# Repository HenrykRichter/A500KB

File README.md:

# A500KB
This project contains the material related to a custom Commodore Amiga Mechanical Keyboard. While the initial development target was the iconic Amiga 500, the keyboard also fits in A3000/A4000 (maybe also A2000) external keyboard enclosures. It features the ability to mount Mitsumi or Cherry switches. The Power, Drive and Caps-Lock LEDs are implemented as 7 individually configurable RGB LEDs. LED configuration is provided by an AmigaOS program that talks to the Keyboard over the regular connection. Headers for two additional low active input sources (e.g. HDD, Network) are also present.

The keyboard may be populated with two options of Switches and associated Keycaps. The first option are the tactile Mitsumi mechanical switches (E25-33-137) and original A2000/3000/4000 keycaps or A1200.net replica keycaps. Please note that the Mitsumi mechanical switches are quite rare. The second option for switches and keycaps is standard Cherry MX or compatibles. In that latter case, the keycaps for the original Amiga layout are hard to obtain. Recently, the user steveed on [Amibay](https://www.amibay.com/threads/amiga-mx-style-keycaps-pcbs.2446001/) has managed to get replica Amiga compatible keycaps ordered from SignaturePlastics. Consequently, the recent designs of the plate are targeted at Cherry MX compatible stabilizers. The PCB still accepts Mitsumi or Cherry MX (3 pin or 5 pin) compatible switches.

If building the full keyboard is not an option, a sub-project of A500KB might be of interest. The controller part of A500KB is also usable as standalone controller for classic Mitsumi keyboards (A500KB Mini). While that A500KB Mini approach won't give the benefit of mechanical switches, it'll offer the custom LED functionality of A500KB.

Please have a look at the README.md in PCB/ for ordering/building notes.

## Requirements

- Amiga 500 or A3000/A4000 keyboard case
- Main PCB and Switchplate PCB
- 96 Keyswitches (Mitsumi or Cherry)
- parts (including AT90USB1287, IS32FL3237, diodes, LEDs and passives)
- suitable LEDs need to be of ARGB type (analog, common anode) such as Würth 150141M173100, Brightek QBLP677-RGB or similar
- 3D Printed parts for LED light guides (transparent) and spacers

## Pictures

## Acknowledgements

Kicad 3D Models and original Footprints imported from:
https://github.com/perigoso/keyswitch-kicad-library

## History

Version 2 of the PCBs addresses several small issues with the prototype. Better fitment is provided for Costar style suports of the larger keys (Shift,Return,Space,Tab etc.). Also, those keys are rotated 90 degrees such that the wire of the supports gets better clearance. The plate PCB got positioning holes for the pins in the top cover of A3000/A4000 keyboards.  Some minor additions were done to the electronics, including larger Diodes and more pullup/down resistors. Version 4 (see below) addresses potential space issues with A500 cases and cabling headers.

A set of 3D printed parts to fit A500KB into the Checkmate external keyboard case has been added in Apr-2025. Please see [3DPrint](https://github.com/HenrykRichter/A500KB/tree/main/3DPrint/Checkmate_KB_Case) for STL files and guidance pictures.

## Caveats

Potential space issues in different styles of A500 cases affected early versions (up to V3) of the design, where the keyboard could only mounted with soldered cables in most A500 cases. Since V4e of the PCB design, the connector J4 has been moved so that it may be populated with an angled pin header and fit all A500 cases as well as external (A2000,A3000,A4000) cases.

## License
The PCB, it's design files and all support code (Amiga, Atmega) are licensed as [CC BY NC SA](https://creativecommons.org/licenses/by-nc-sa/4.0/deed.en).

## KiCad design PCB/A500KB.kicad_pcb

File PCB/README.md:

# A500KB Building Notes
This project contains the material related to a custom Commodore Amiga Mechanical Keyboard. While the initial development target was the iconic Amiga 500, the keyboard also fits in A3000/A4000 (maybe also A2000) external keyboard enclosures. It features the ability to mount Mitsumi or Cherry switches. The Power, Drive and Caps-Lock LEDs are implemented as 7 individually configurable RGB LEDs. LED configuration is provided by an AmigaOS program that talks to the Keyboard over the regular connection. Headers for two additional low active input sources (e.g. HDD, Network) are also present.

The two variants of the PCBs in this repository are discussed below. In a nutshell: order PCB and plate for the full keyboard or just the A500KBMini PCB for the standalone controller.

## A500KB (full)

### PCB ordering

**Caution** There are two styles of Keyboard and Plate designs. The one with the suffix "US" is designed specifically for large left Shift (2.75U) and the "BigAss" mirrored L style return key. Should your keycap set include an ISO-style return key (like in most of my pictures), please choose the variant without "US" suffix. See below for comparison pictures towards Keycap styles, if still unsure.

- 1 PCB from A500KB\_Gerber, 2 layer PCB in FR4, 1.2mm thickness for a little more space in bottom case (standard 1.6mm will still be compatible)
- 1 PCB from A500KBPlate\_Gerber, 1 layer PCB in FR4 or Alu, 1mm thickness for PCB or plate mounted MX stabilizers _OR_ A500KBPlate\_Gerber\_V2D.zip for Costar style stabilizers

Starting with V5, there is also a US version of PCB and Plate designs. The US variant includes a large LShift (2.75U) and a large Return (inverted L). Please note that the respective keycaps for ISO Keyboards will not fit on the US version and vice versa.

### 3D printing

The 3D printed parts are in the 3DPrint/ subfolder. Which of those files are to be printed depends on the target enclosure. Please note that bolts and nuts are required for mounting. 
The keyboard framing spacers are designed for countersunk M2.5 bolts with a total length of 5mm. 
The LED frame is to be mounted by flathead M2 bolts with a total length of 5mm and matching nuts.

As of A500KB V4, the 3D printed parts have been unified. The side spacers will fit A500 (and reproduction cases), as well as at least most of the external keyboard cases (tested: A2000,A3000,A4000 Mitsumi cases).

Four parts are designed for all keyboard types: 
- Keyboard\_Spacer\_L\_F2025  - left side of keyboard
- Keyboard\_Spacer\_R\_F2025  - right side of keyboard
- Keyboard\_Spacer\_VL\_F2025 - front left below spacebar
- Keyboard\_Spacer\_VR\_F2025 - front right below cursor keys

A500
- Keyboard\_LEDs\_Rahmen - frame for holding the LED lenses
- Keyboard\_LEDs - LED lenses to be printed (twice!) in transparent filament or resin. Keep infill low.

You also might consider to look at Spacebar\_ExtraSprings for Mitsumi mechanical based builds. This part allows to place additional springs under the space bar in the same way that was present with Mitsumi Amiga keyboards. 

Also of relevance for Mitsumi builds is Keyboard\_CapsLockLED to be printed in transparent filament or resin. This light guide is supposed to point towards the clear dot on the CapsLock key from underneath.

One CDTV Keyboard I came across had studs in its lower case which were about 2mm shorter than those of other 
A2000-4000 keyboards I encountered. The A500KB might sit a bit too low in such CDTV keyboard enclosures. Simply place
three 3D printed adapters of CDTVKeyboard\_Stud\_Adapter.stl on the top row studs in that case.

### Parts

- Please see schematics and/or A500KB.csv for the latest list. All needed components were marked active at the last check with common distributors (like Digikey or Mouser).
- The 7 RGB LEDs need to be of RGBA type (i.e. common Anode) and can be mounted as PLCC or with leads.
- Choose between D1 and D69, depending on switches and keycaps. For CherryMX switches (with SMD LED provision), D69 would be a good choice. D1 is better suited for Mitsumi switches and associated keycaps.
- C15/C16 are not needed.
- The 1x31 flat cable connector (J1) is not needed and stays unpopulated
- Screw-In PCB mounted stabilizers are recommended for Cherry MX and compatible
- see below for a description in which cases R6/R10/R11 need to be installed
- an iBOM is provided as PCB/bom/ibom.html as soldering aid. Please download before use.

### Building

- Solder the SMD components first. 
- Populate either D1 or D69 for CapsLock LED, not both. D2 as classic CapsLock LED is optional. D2 can also be disabled in firmware, if desired (i.e. populate R10 to disable D2).
- Install R6 with 390R for use of RGB LEDs at the positions of Power LED and Floppy LED. Leave R6 open when placing classic Commodore A500 Green/Orange or Red/Green LEDs.
- V3b/V4: install R11 when digital LEDs (SK9822 or APA102) are mounted to D70-D84. Leave R11 open, otherwise

After placing the SMD components, flash the ATMega firmware and verify that the keyboard PCB works.
- Option A) connect by USB to some PC and shorten the pins of the individual keys
- Option B) add A500 cable to J4 and test with AmigaTestKit or similar

Please note that diode reworking after the plate was placed and keyswitches were soldered is not a job I'd look forward to. Therefore, diode soldering and orientation should be verified before going further (!)

For CherryMX based builds, place the PCB mounted stabilizers including their wires in the next step. Screw-In type stabilizers should be preferred. 8U stabilizer wires are not commonly available. Hence, it might be necessary to custom-bend the spacebar wire (133.4mm wide, 1.5-1.6mm diameter).

Afterwards, the keyswitches may be added. It is suggested to place four keyswitches in the corners and one in the middle at first. This tends to help aligning the plate over the main PCB. 

Add the 3D printed spacers, LED frame and lenses.

Consider some electric short protection as the last step after fitment tests are done and possibly remaining THT parts (like J5) are in. For me, two layers of Kapton (or generic Polyimide) tape have been working well. The Kapton doesn't add significant thickness to the main PCB.

### PCB / Plate variant choice

The following pictures should help to decide which PCB and Plate variant to obtain. The critical part in this choice is the Return key, where the mounting points differ significantly between the international version (ISO) version and the US (ANSI) layout.

## A500KBMini

A500KBMini is a little less demanding in the build procedure. There is, however a showstopper for prospective builds. None of the shops I am aware of carries the 1x31 angled FFC connector to be required for A500 Mitsumi Keyboards. Scavenging from broken Mitsumi keyboards might be an option.

### PCB ordering

- 1 PCB from A500KBMini\_Gerber, 2 layer PCB in FR4, 1mm-1.6mm thickness 

### 3D Printing
- Keyboard\_LEDs\_Rahmen as frame for holding the LED lenses
- Keyboard\_LEDs LED lenses to be printed (twice!) in transparent filament or resin

### Parts

- Please see schematics and/or A500KB.csv for the latest list. Exclude the 58 Diodes used for NKRO on the full keyboard. Except from the FFC connector, all other needed components were marked active at the last check with common distributors (like Digikey or Mouser).
- The 6 RGB LEDs need to be of RGBA type (i.e. common anode) and can be mounted as PLCC or with leads.
- C15/C16 are not needed.
- The 1x31 flat cable connector (J1) needs to be obtained and fitted.
- R10/R11 stay unpopulated

### Building

- Solder the SMD components first. 
- Install R6 with 390R for use of RGB LEDs at the positions of Power LED and Floppy LED. Leave R6 open when placing classic A500 Green/Orange or Red/Green LEDs.

After placing the SMD components, flash the ATMega firmware and verify that the keyboard PCB works.

Add the 3D printed LED frame and lenses.

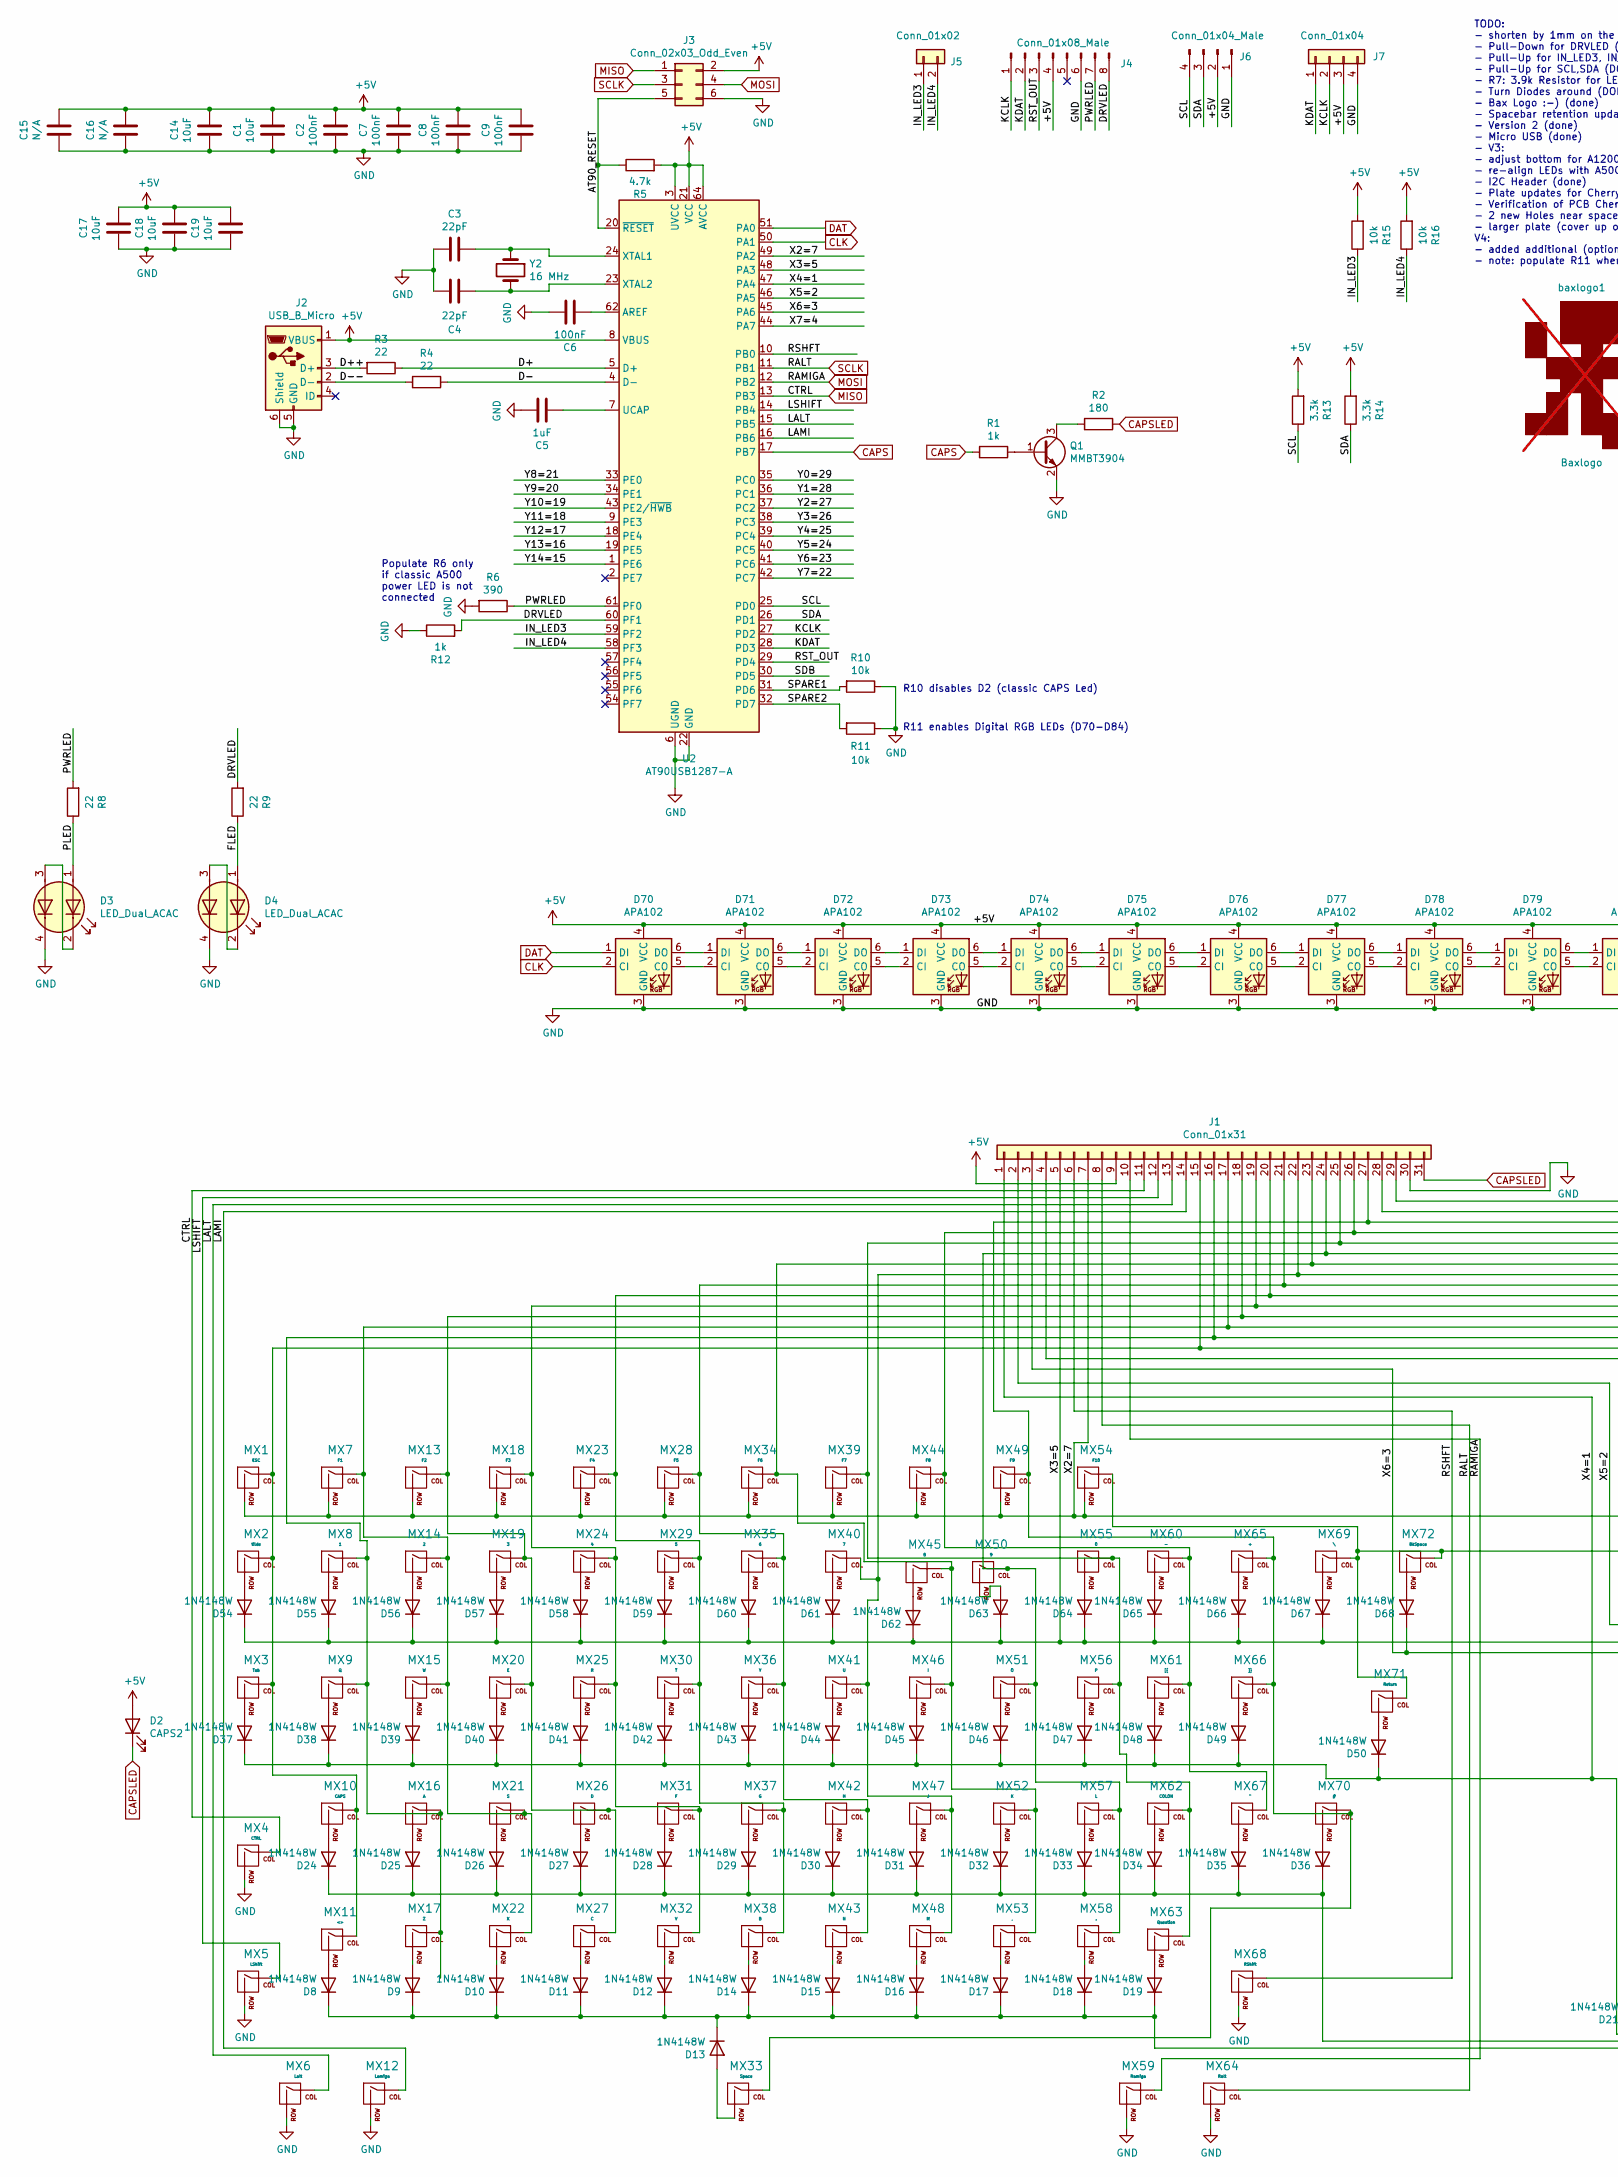
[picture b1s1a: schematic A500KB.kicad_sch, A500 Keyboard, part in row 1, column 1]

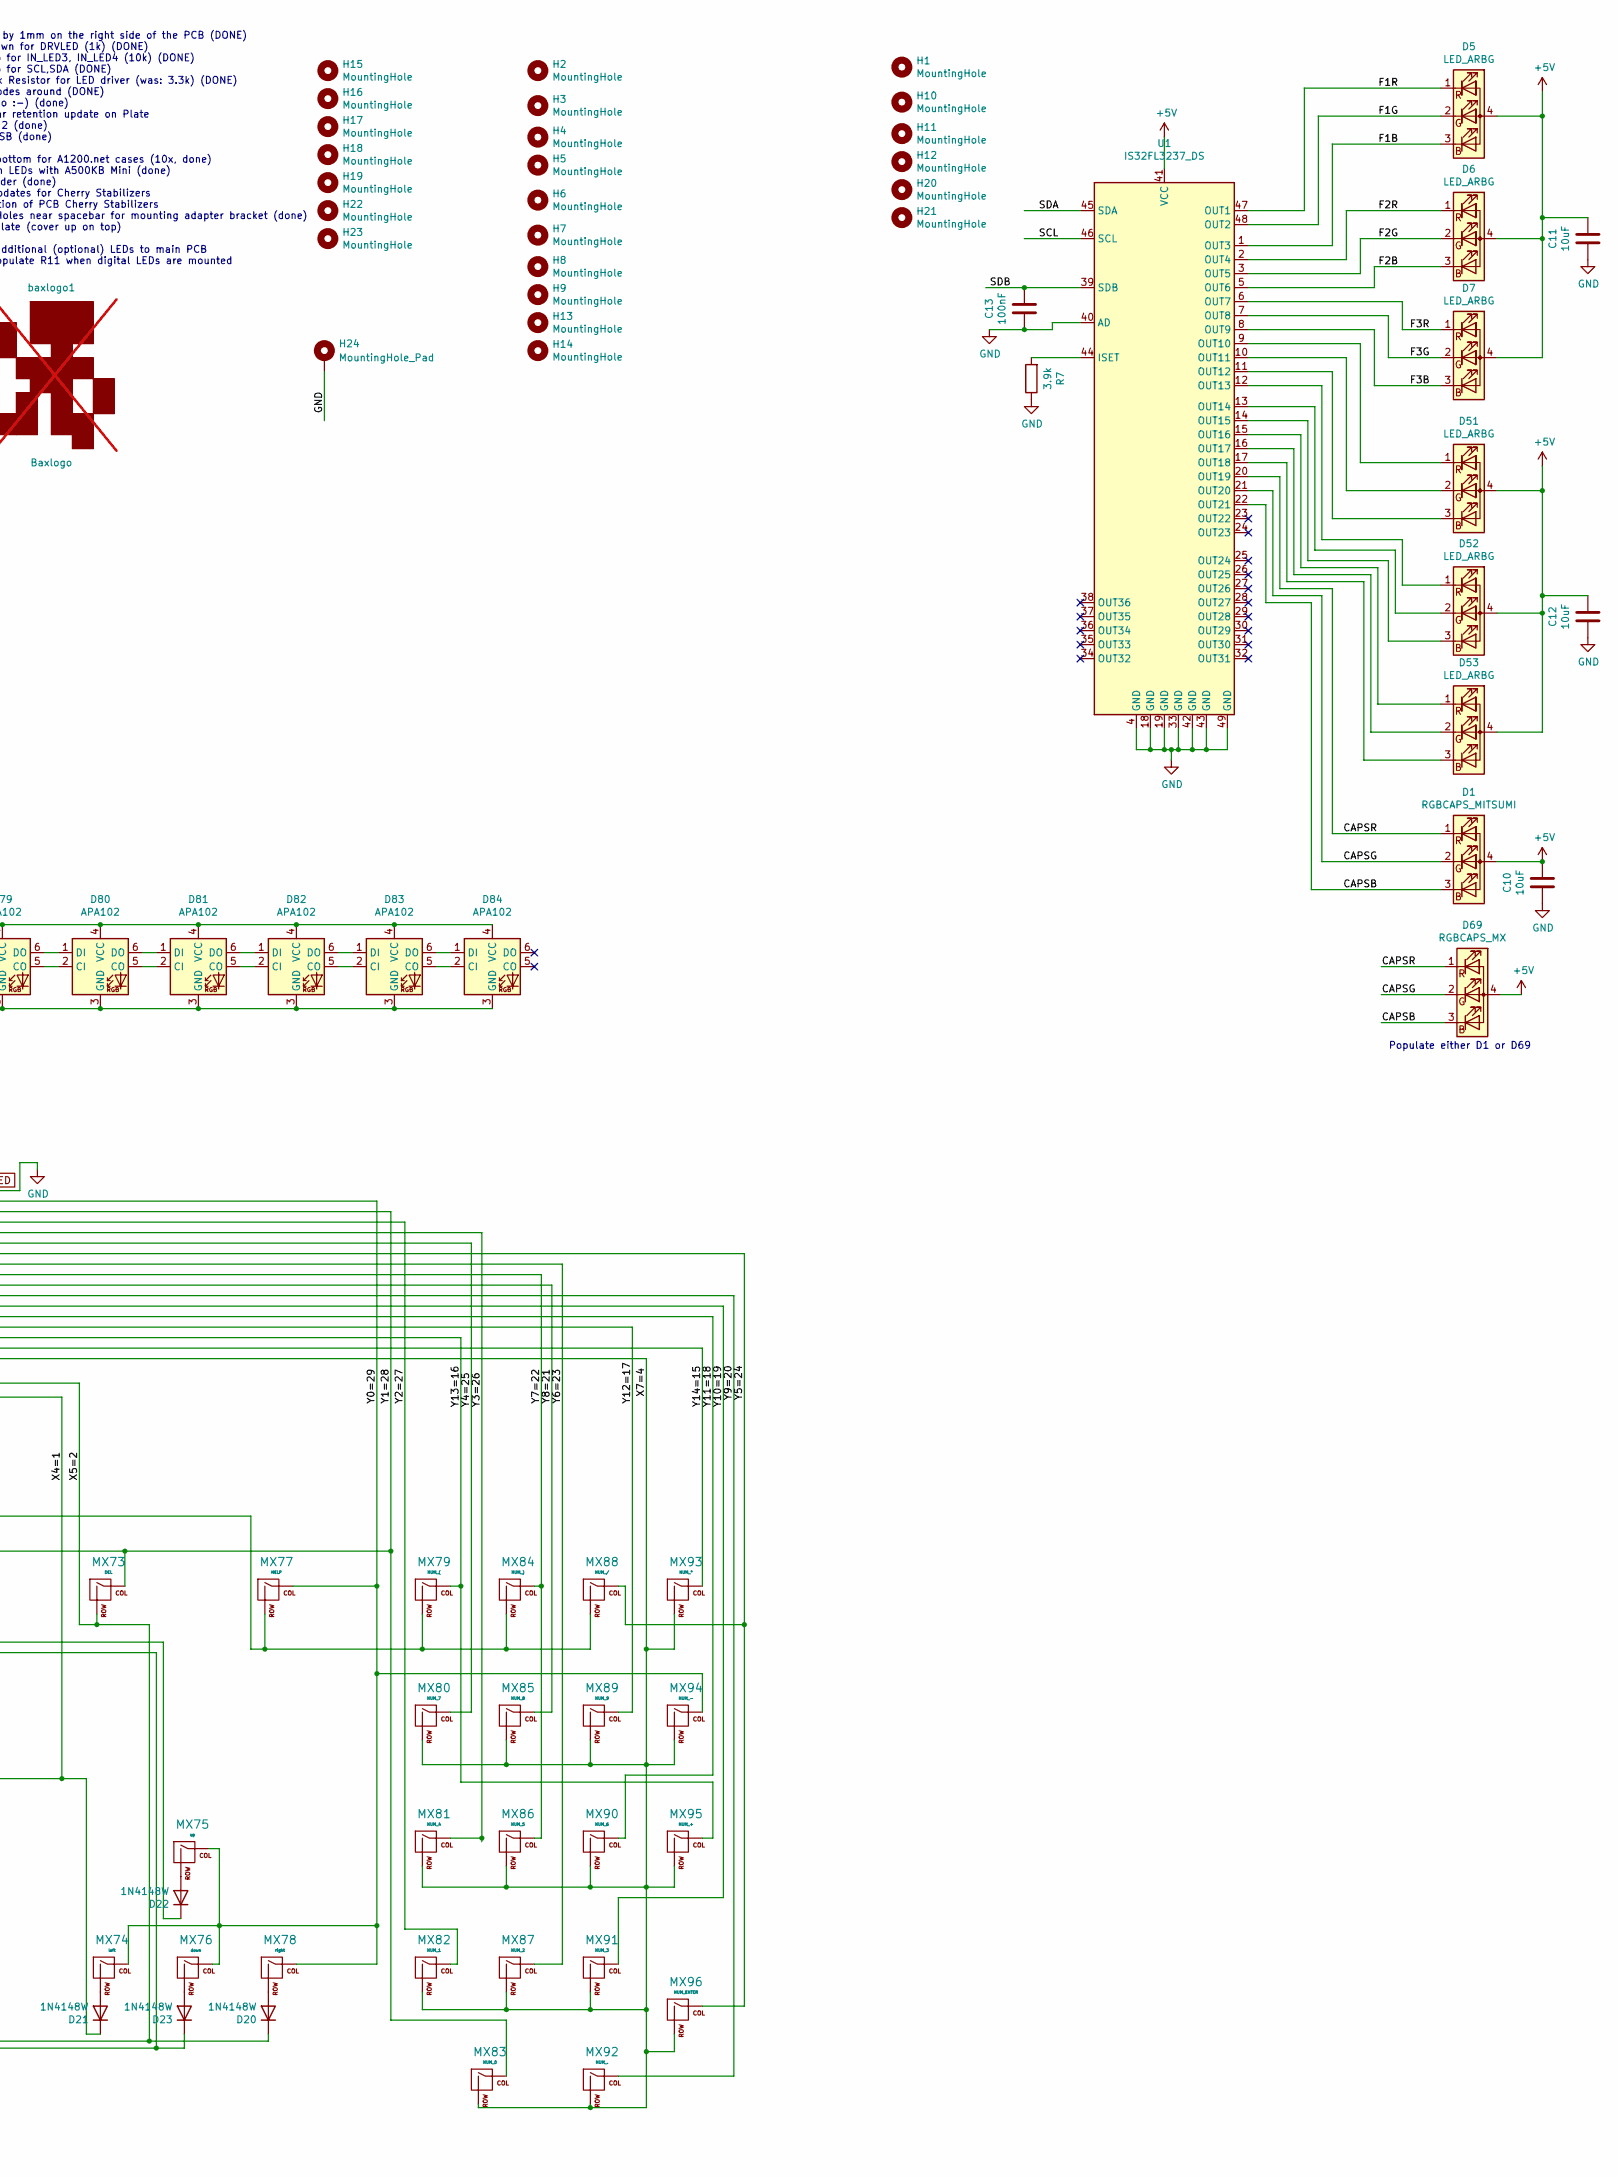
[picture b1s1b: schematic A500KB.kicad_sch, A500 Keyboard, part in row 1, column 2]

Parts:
C1, C10, C11, C12, C14, C17, C18, C19: 10uF; C_0805_2012Metric_Pad1.18x1.45mm_HandSolder; LCSC C15850
C2, C6, C7, C8, C9, C13: 100nF; C_0805_2012Metric_Pad1.18x1.45mm_HandSolder; LCSC C49678
C3, C4: 22pF; C_0805_2012Metric_Pad1.18x1.45mm_HandSolder; LCSC C1804
C5: 1uF; C_0805_2012Metric_Pad1.18x1.45mm_HandSolder; LCSC C28323
C15, C16: N/A; C_Elec_6.3x5.8
D1: RGBCAPS_MITSUMI; LED_Cree-PLCC4_3.2x2.8mm_CCW; digikey 732-4998-1-ND
D2: CAPS2; D_0805_2012Metric_Pad1.15x1.40mm_HandSolder; LCSC C688883
D3, D4: LED_Dual_ACAC; LED_DUAL_A500
D5: LED_ARBG; LED_Cree-PLCC4_3.2x2.8mm_CCW; digikey 1516-1195-1-ND
D6, D7, D51, D52, D53: LED_ARBG; LED_Cree-PLCC4_3.2x2.8mm_CCW; LCSC C5342281
D8, D9, D10, D11, D12, D13, D14, D15, D16, D17, D18, D19, D20, D21, D22, D23, D24, D25, D26, D27, D28, D29, D30, D31, D32, D33, D34, D35, D36, D37, D38, D39, D40, D41, D42, D43, D44, D45, D46, D47, D48, D49, D50, D54, D55, D56, D57, D58, D59, D60, D61, D62, D63, D64, D65, D66, D67, D68: 1N4148W; D_SOD-123; LCSC C444720
D69: RGBCAPS_MX; LED_Cree-PLCC4_3.2x2.8mm_CCW; digikey 732-4998-1-ND
D70, D71, D72, D73, D74, D75, D76, D77, D78, D79, D80, D81, D82, D83, D84: APA102; LED_RGB_5050-6; LCSC C5378730
H1, H2, H3, H4, H5, H6, H7, H8, H9, H10, H11, H12, H13, H14, H20, H21: MountingHole; MountingHole_3.2mm_M3_Small_Bax
H15, H16, H17, H18, H22, H23: MountingHole; MountingHole_2.5mm
H19: MountingHole; MountingHole_4.3mm_M4
H24: MountingHole_Pad; MountingHole_2.5mm_Pad_TopBottom
J1: Conn_01x31; FFC-1.25mm-Molex-39-53-2314
J2: USB_B_Micro; USB_Micro-B_Molex-105017-0001; Mouser 538-105017-0001
J3: Conn_02x03_Odd_Even; PinHeader_2x03_P2.54mm_Vertical; LCSC C32713276
J4: Conn_01x08_Male; PinHeader_1x08_P2.54mm_Vertical; LCSC C2935933
J5: Conn_01x02; PinHeader_1x02_P2.54mm_Vertical
J6: Conn_01x04_Male; PinHeader_1x04_P2.54mm_Vertical
J7: Conn_01x04; JST_EH_S4B-EH_1x04_P2.50mm_Horizontal; LCSC C265068
MX1: ESC; MXMitsumi-1U-NoLED
MX2: tilde; MXMitsumi-1.5U-NoLED
MX3: Tab; MXMitsumi-2U-NoLED
MX4: CTRL; MXMitsumi-1.25U-NoLED
MX5: LShift; MXMitsumi-1.75U-NoLED
MX6: Lalt; MXMitsumi-1.25U-NoLED
MX7: F1; MXMitsumi-1.25U-NoLED
MX8: 1; MXMitsumi-1U-NoLED
MX9: Q; MXMitsumi-1U-NoLED
MX10: CAPS; MXMitsumi-1U-NoLED
MX11: <>; MXMitsumi-1U-NoLED
MX12: Lamiga; MXMitsumi-1.25U-NoLED
MX13: F2; MXMitsumi-1.25U-NoLED
MX14: 2; MXMitsumi-1U-NoLED
MX15: W; MXMitsumi-1U-NoLED
MX16: A; MXMitsumi-1U-NoLED
MX17: Z; MXMitsumi-1U-NoLED
MX18: F3; MXMitsumi-1.25U-NoLED
MX19: 3; MXMitsumi-1U-NoLED
MX20: E; MXMitsumi-1U-NoLED
MX21: S; MXMitsumi-1U-NoLED
MX22: X; MXMitsumi-1U-NoLED
MX23: F4; MXMitsumi-1.25U-NoLED
MX24: 4; MXMitsumi-1U-NoLED
MX25: R; MXMitsumi-1U-NoLED
MX26: D; MXMitsumi-1U-NoLED
MX27: C; MXMitsumi-1U-NoLED
MX28: F5; MXMitsumi-1.25U-NoLED
MX29: 5; MXMitsumi-1U-NoLED
MX30: T; MXMitsumi-1U-NoLED
MX31: F; MXMitsumi-1U-NoLED
MX32: V; MXMitsumi-1U-NoLED
MX33: Space; MXMitsumi-9U-NoLED
MX34: F6; MXMitsumi-1.25U-NoLED
MX35: 6; MXMitsumi-1U-NoLED
MX36: Y; MXMitsumi-1U-NoLED
MX37: G; MXMitsumi-1U-NoLED
MX38: B; MXMitsumi-1U-NoLED
MX39: F7; MXMitsumi-1.25U-NoLED
MX40: 7; MXMitsumi-1U-NoLED
MX41: U; MXMitsumi-1U-NoLED
MX42: H; MXMitsumi-1U-NoLED
MX43: N; MXMitsumi-1U-NoLED
MX44: F8; MXMitsumi-1.25U-NoLED
MX45: 8; MXMitsumi-1U-NoLED
MX46: I; MXMitsumi-1U-NoLED
MX47: J; MXMitsumi-1U-NoLED
MX48: M; MXMitsumi-1U-NoLED
MX49: F9; MXMitsumi-1.25U-NoLED
MX50: 9; MXMitsumi-1U-NoLED
MX51: O; MXMitsumi-1U-NoLED
MX52: K; MXMitsumi-1U-NoLED
MX53: ,; MXMitsumi-1U-NoLED
MX54: F10; MXMitsumi-1.25U-NoLED
MX55: 0; MXMitsumi-1U-NoLED
MX56: P; MXMitsumi-1U-NoLED
MX57: L; MXMitsumi-1U-NoLED
MX58: .; MXMitsumi-1U-NoLED
MX59: Ramiga; MXMitsumi-1.25U-NoLED
MX60: -; MXMitsumi-1U-NoLED
MX61: [{; MXMitsumi-1U-NoLED
MX62: COLON; MXMitsumi-1U-NoLED
MX63: Question; MXMitsumi-1U-NoLED
MX64: Ralt; MXMitsumi-1.25U-NoLED
MX65: +; MXMitsumi-1U-NoLED
MX66: ]}; MXMitsumi-1U-NoLED
MX67: "; MXMitsumi-1U-NoLED
MX68: RShift; MXMitsumi-2.75U-NoLED
MX69: \; MXMitsumi-1U-NoLED
MX70: #; MXMitsumi-1U-NoLED
MX71: Return; MXMitsumi-ISO-NoLED
MX72: BkSpace; MXMitsumi-1U-NoLED
MX73: DEL; MXMitsumi-1.5U-NoLED
MX74: left; MXMitsumi-1U-NoLED
MX75: up; MXMitsumi-1U-NoLED
MX76: down; MXMitsumi-1U-NoLED
MX77: HELP; MXMitsumi-1.5U-NoLED
MX78: right; MXMitsumi-1U-NoLED
MX79: NUM_(; MXMitsumi-1U-NoLED
MX80: NUM_7; MXMitsumi-1U-NoLED
MX81: NUM_4; MXMitsumi-1U-NoLED
MX82: NUM_1; MXMitsumi-1U-NoLED
MX83: NUM_0; MXMitsumi-2U-NoLED
MX84: NUM_); MXMitsumi-1U-NoLED
MX85: NUM_8; MXMitsumi-1U-NoLED
MX86: NUM_5; MXMitsumi-1U-NoLED
MX87: NUM_2; MXMitsumi-1U-NoLED
MX88: NUM_/; MXMitsumi-1U-NoLED
MX89: NUM_9; MXMitsumi-1U-NoLED
MX90: NUM_6; MXMitsumi-1U-NoLED
MX91: NUM_3; MXMitsumi-1U-NoLED
MX92: NUM_.; MXMitsumi-1U-NoLED
MX93: NUM_*; MXMitsumi-1U-NoLED
MX94: NUM_-; MXMitsumi-1U-NoLED
MX95: NUM_+; MXMitsumi-1U-NoLED
MX96: NUM_ENTER; MXMitsumi-2U-VerticalStabilizers-NoLED
Q1: MMBT3904; SOT-23; LCSC C20526
R1, R12: 1k; R_0805_2012Metric_Pad1.20x1.40mm_HandSolder; LCSC C17513
R2: 180; R_0805_2012Metric_Pad1.20x1.40mm_HandSolder; LCSC C25270
R3, R4, R8, R9: 22; R_0805_2012Metric_Pad1.20x1.40mm_HandSolder; LCSC C17561
R5: 4.7k; R_0805_2012Metric_Pad1.20x1.40mm_HandSolder; LCSC C17673
R6: 390; R_0805_2012Metric_Pad1.20x1.40mm_HandSolder; LCSC C17655
R7: 3.9k; R_0805_2012Metric_Pad1.20x1.40mm_HandSolder; LCSC C17614
R10, R11, R15, R16: 10k; R_0805_2012Metric_Pad1.20x1.40mm_HandSolder; LCSC C17414
R13, R14: 3.3k; R_0805_2012Metric_Pad1.20x1.40mm_HandSolder; LCSC C26010
U1: IS32FL3237_DS; TQFP-48-1EP_7x7mm_P0.5mm_EP5x5mm_ThermalVias; LCSC C3189535
U2: AT90USB1287-A; TQFP-64_14x14mm_P0.8mm; LCSC C619282
Y2: 16 MHz; Crystal_SMD_TXC_7A-2Pin_5x3.2mm; LCSC C112572
baxlogo1: Baxlogo; baxlogo; not fitted

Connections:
+5V: C1.1, C2.1, C7.1, C8.1, C9.1, C10.1, C11.1, C12.1, C14.1, C15.1, C16.1, C17.1, C18.1, C19.1, D1.4 (A), D2.2 (A), D5.4 (A), D6.4 (A), D7.4 (A), D51.4 (A), D52.4 (A), D53.4 (A), D69.4 (A), D70.4 (VCC), D71.4 (VCC), D72.4 (VCC), D73.4 (VCC), D74.4 (VCC), D75.4 (VCC), D76.4 (VCC), D77.4 (VCC), D78.4 (VCC), D79.4 (VCC), D80.4 (VCC), D81.4 (VCC), D82.4 (VCC), D83.4 (VCC), D84.4 (VCC), J1.9, J2.1 (VBUS), J3.2, J4.4, J6.2, J7.3, R5.2, R13.2, R14.2, R15.2, R16.2, U1.41 (VCC), U2.3 (UVCC), U2.8 (VBUS), U2.21 (VCC), U2.52 (VCC), U2.64 (AVCC)
/AT90_RESET: J3.5, R5.1, U2.20 (~RESET)
/CAPSB: D1.3 (BK), D69.3 (BK), U1.22 (OUT21)
/CAPSG: D1.2 (GK), D69.2 (GK), U1.21 (OUT20)
/CAPSR: D1.1 (RK), D69.1 (RK), U1.20 (OUT19)
/D+: R3.1, U2.5 (D+)
/D++: J2.3 (D+), R3.2
/D-: R4.1, U2.4 (D-)
/D--: J2.2 (D-), R4.2
/DRVLED: J4.8, R9.2, R12.2, U2.60 (PF1)
/F1B: D5.3 (BK), U1.1 (OUT3)
/F1G: D5.2 (GK), U1.48 (OUT2)
/F1R: D5.1 (RK), U1.47 (OUT1)
/F2B: D6.3 (BK), U1.5 (OUT6)
/F2G: D6.2 (GK), U1.3 (OUT5)
/F2R: D6.1 (RK), U1.2 (OUT4)
/F3B: D7.3 (BK), U1.8 (OUT9)
/F3G: D7.2 (GK), U1.7 (OUT8)
/F3R: D7.1 (RK), U1.6 (OUT7)
/FLED: D4.1 (A1), R9.1
/IN_LED3: J5.1, R15.1, U2.59 (PF2)
/IN_LED4: J5.2, R16.1, U2.58 (PF3)
/KCLK: J4.1, J7.2, U2.27 (PD2)
/KDAT: J4.2, J7.1, U2.28 (PD3)
/LALT: J1.13, MX6.1 (COL), U2.15 (PB5)
/LAMI: J1.14, MX12.1 (COL), U2.16 (PB6)
/LSHIFT: J1.12, MX5.1 (COL), U2.14 (PB4)
/PLED: D3.1 (A1), R8.1
/PWRLED: J4.7, R6.1, R8.2, U2.61 (PF0)
/RSHFT: J1.6, MX68.1 (COL), U2.10 (PB0)
/RST_OUT: J4.3, U2.29 (PD4)
/SCL: J6.4, R13.1, U1.46 (SCL), U2.25 (PD0)
/SDA: J6.3, R14.1, U1.45 (SDA), U2.26 (PD1)
/SDB: C13.1, U1.39 (SDB), U2.30 (PD5)
/SPARE1: R10.2, U2.31 (PD6)
/SPARE2: R11.2, U2.32 (PD7)
/X2=7: J1.7, MX1.2 (ROW), MX7.2 (ROW), MX13.2 (ROW), MX18.2 (ROW), MX23.2 (ROW), MX28.2 (ROW), MX34.2 (ROW), MX39.2 (ROW), MX44.2 (ROW), MX49.2 (ROW), MX54.2 (ROW), MX77.2 (ROW), MX79.2 (ROW), MX84.2 (ROW), MX88.2 (ROW), U2.49 (PA2)
/X3=5: D22.1 (K), D54.1 (K), D55.1 (K), D56.1 (K), D57.1 (K), D58.1 (K), D59.1 (K), D60.1 (K), D61.1 (K), D62.1 (K), D63.1 (K), D64.1 (K), D65.1 (K), D66.1 (K), D67.1 (K), J1.5, U2.48 (PA3)
/X4=1: D21.1 (K), D37.1 (K), D38.1 (K), D39.1 (K), D40.1 (K), D41.1 (K), D42.1 (K), D43.1 (K), D44.1 (K), D45.1 (K), D46.1 (K), D47.1 (K), D48.1 (K), D49.1 (K), D50.1 (K), J1.1, U2.47 (PA4)
/X5=2: D20.1 (K), D24.1 (K), D25.1 (K), D26.1 (K), D27.1 (K), D28.1 (K), D29.1 (K), D30.1 (K), D31.1 (K), D32.1 (K), D33.1 (K), D34.1 (K), D35.1 (K), D36.1 (K), J1.2, MX73.2 (ROW), U2.46 (PA5)
/X6=3: D8.1 (K), D9.1 (K), D10.1 (K), D11.1 (K), D12.1 (K), D13.1 (K), D14.1 (K), D15.1 (K), D16.1 (K), D17.1 (K), D18.1 (K), D19.1 (K), D23.1 (K), D68.1 (K), J1.3, U2.45 (PA6)
/X7=4: J1.4, MX80.2 (ROW), MX81.2 (ROW), MX82.2 (ROW), MX83.2 (ROW), MX85.2 (ROW), MX86.2 (ROW), MX87.2 (ROW), MX89.2 (ROW), MX90.2 (ROW), MX91.2 (ROW), MX92.2 (ROW), MX93.2 (ROW), MX94.2 (ROW), MX95.2 (ROW), MX96.2 (ROW), U2.44 (PA7)
/Y0=29: J1.29, MX74.1 (COL), MX75.1 (COL), MX76.1 (COL), MX77.1 (COL), MX78.1 (COL), MX94.1 (COL), U2.35 (PC0)
/Y1=28: J1.28, MX54.1 (COL), MX69.1 (COL), MX71.1 (COL), MX72.1 (COL), MX73.1 (COL), MX83.1 (COL), U2.36 (PC1)
/Y2=27: J1.27, MX33.1 (COL), MX49.1 (COL), MX65.1 (COL), MX66.1 (COL), MX70.1 (COL), MX82.1 (COL), U2.37 (PC2)
/Y3=26: J1.26, MX44.1 (COL), MX60.1 (COL), MX61.1 (COL), MX67.1 (COL), MX81.1 (COL), U2.38 (PC3)
/Y4=25: J1.25, MX39.1 (COL), MX55.1 (COL), MX56.1 (COL), MX62.1 (COL), MX63.1 (COL), MX80.1 (COL), U2.39 (PC4)
/Y5=24: J1.24, MX50.1 (COL), MX51.1 (COL), MX57.1 (COL), MX58.1 (COL), MX88.1 (COL), MX96.1 (COL), U2.40 (PC5)
/Y6=23: J1.23, MX34.1 (COL), MX45.1 (COL), MX46.1 (COL), MX52.1 (COL), MX53.1 (COL), MX87.1 (COL), U2.41 (PC6)
/Y7=22: J1.22, MX40.1 (COL), MX41.1 (COL), MX47.1 (COL), MX48.1 (COL), MX84.1 (COL), MX86.1 (COL), U2.42 (PC7)
/Y8=21: J1.21, MX28.1 (COL), MX35.1 (COL), MX36.1 (COL), MX42.1 (COL), MX43.1 (COL), MX85.1 (COL), U2.33 (PE0)
/Y9=20: J1.20, MX23.1 (COL), MX29.1 (COL), MX30.1 (COL), MX37.1 (COL), MX38.1 (COL), MX92.1 (COL), U2.34 (PE1)
/Y10=19: J1.19, MX18.1 (COL), MX24.1 (COL), MX25.1 (COL), MX31.1 (COL), MX32.1 (COL), MX91.1 (COL), U2.43 (PE2/~HWB)
/Y11=18: J1.18, MX13.1 (COL), MX19.1 (COL), MX20.1 (COL), MX26.1 (COL), MX27.1 (COL), MX90.1 (COL), U2.9 (PE3)
/Y12=17: J1.17, MX7.1 (COL), MX14.1 (COL), MX15.1 (COL), MX21.1 (COL), MX22.1 (COL), MX89.1 (COL), U2.18 (PE4)
/Y13=16: J1.16, MX8.1 (COL), MX9.1 (COL), MX16.1 (COL), MX17.1 (COL), MX79.1 (COL), MX95.1 (COL), U2.19 (PE5)
/Y14=15: J1.15, MX1.1 (COL), MX2.1 (COL), MX3.1 (COL), MX10.1 (COL), MX11.1 (COL), MX93.1 (COL), U2.1 (PE6)
CAPS: R1.2, U2.17 (PB7)
CAPSLED: D2.1 (K), J1.31, R2.1
GND: C1.2, C2.2, C3.2, C4.1, C5.1, C6.1, C7.2, C8.2, C9.2, C10.2, C11.2, C12.2, C13.2, C14.2, C15.2, C16.2, C17.2, C18.2, C19.2, D3.4 (K2), D4.4 (K2), D70.3 (GND), D71.3 (GND), D72.3 (GND), D73.3 (GND), D74.3 (GND), D75.3 (GND), D76.3 (GND), D77.3 (GND), D78.3 (GND), D79.3 (GND), D80.3 (GND), D81.3 (GND), D82.3 (GND), D83.3 (GND), D84.3 (GND), H24.1, J1.30, J2.5 (GND), J2.6 (Shield), J3.6, J4.6, J6.1, J7.4, MX4.2 (ROW), MX5.2 (ROW), MX6.2 (ROW), MX12.2 (ROW), MX59.2 (ROW), MX64.2 (ROW), MX68.2 (ROW), Q1.2 (E), R6.2, R7.1, R10.1, R11.1, R12.1, U1.4 (GND), U1.18 (GND), U1.19 (GND), U1.33 (GND), U1.40 (AD), U1.42 (GND), U1.43 (GND), U1.49 (GND), U2.6 (UGND), U2.22 (GND), U2.53 (GND), U2.63 (GND)
MISO: J1.11, J3.1, MX4.1 (COL), U2.13 (PB3)
MOSI: J1.10, J3.4, MX59.1 (COL), U2.12 (PB2)
unnamed: C3.1, U2.24 (XTAL1), Y2.1
unnamed: C4.2, U2.23 (XTAL2), Y2.2
unnamed: C5.2, U2.7 (UCAP)
unnamed: C6.2, U2.62 (AREF)
unnamed: D3.2 (K1), D3.3 (A2)
unnamed: D4.2 (K1), D4.3 (A2)
unnamed: D8.2 (A), MX11.2 (ROW)
unnamed: D9.2 (A), MX17.2 (ROW)
unnamed: D10.2 (A), MX22.2 (ROW)
unnamed: D11.2 (A), MX27.2 (ROW)
unnamed: D12.2 (A), MX32.2 (ROW)
unnamed: D13.2 (A), MX33.2 (ROW)
unnamed: D14.2 (A), MX38.2 (ROW)
unnamed: D15.2 (A), MX43.2 (ROW)
unnamed: D16.2 (A), MX48.2 (ROW)
unnamed: D17.2 (A), MX53.2 (ROW)
unnamed: D18.2 (A), MX58.2 (ROW)
unnamed: D19.2 (A), MX63.2 (ROW)
unnamed: D20.2 (A), MX78.2 (ROW)
unnamed: D21.2 (A), MX74.2 (ROW)
unnamed: D22.2 (A), MX75.2 (ROW)
unnamed: D23.2 (A), MX76.2 (ROW)
unnamed: D24.2 (A), MX10.2 (ROW)
unnamed: D25.2 (A), MX16.2 (ROW)
unnamed: D26.2 (A), MX21.2 (ROW)
unnamed: D27.2 (A), MX26.2 (ROW)
unnamed: D28.2 (A), MX31.2 (ROW)
unnamed: D29.2 (A), MX37.2 (ROW)
unnamed: D30.2 (A), MX42.2 (ROW)
unnamed: D31.2 (A), MX47.2 (ROW)
unnamed: D32.2 (A), MX52.2 (ROW)
unnamed: D33.2 (A), MX57.2 (ROW)
unnamed: D34.2 (A), MX62.2 (ROW)
unnamed: D35.2 (A), MX67.2 (ROW)
unnamed: D36.2 (A), MX70.2 (ROW)
unnamed: D37.2 (A), MX3.2 (ROW)
unnamed: D38.2 (A), MX9.2 (ROW)
unnamed: D39.2 (A), MX15.2 (ROW)
unnamed: D40.2 (A), MX20.2 (ROW)
unnamed: D41.2 (A), MX25.2 (ROW)
unnamed: D42.2 (A), MX30.2 (ROW)
unnamed: D43.2 (A), MX36.2 (ROW)
unnamed: D44.2 (A), MX41.2 (ROW)
unnamed: D45.2 (A), MX46.2 (ROW)
unnamed: D46.2 (A), MX51.2 (ROW)
unnamed: D47.2 (A), MX56.2 (ROW)
unnamed: D48.2 (A), MX61.2 (ROW)
unnamed: D49.2 (A), MX66.2 (ROW)
unnamed: D50.2 (A), MX71.2 (ROW)
unnamed: D51.1 (RK), U1.9 (OUT10)
unnamed: D51.2 (GK), U1.10 (OUT11)
unnamed: D51.3 (BK), U1.11 (OUT12)
unnamed: D52.1 (RK), U1.12 (OUT13)
unnamed: D52.2 (GK), U1.13 (OUT14)
unnamed: D52.3 (BK), U1.14 (OUT15)
unnamed: D53.1 (RK), U1.15 (OUT16)
unnamed: D53.2 (GK), U1.16 (OUT17)
unnamed: D53.3 (BK), U1.17 (OUT18)
unnamed: D54.2 (A), MX2.2 (ROW)
unnamed: D55.2 (A), MX8.2 (ROW)
unnamed: D56.2 (A), MX14.2 (ROW)
unnamed: D57.2 (A), MX19.2 (ROW)
unnamed: D58.2 (A), MX24.2 (ROW)
unnamed: D59.2 (A), MX29.2 (ROW)
unnamed: D60.2 (A), MX35.2 (ROW)
unnamed: D61.2 (A), MX40.2 (ROW)
unnamed: D62.2 (A), MX45.2 (ROW)
unnamed: D63.2 (A), MX50.2 (ROW)
unnamed: D64.2 (A), MX55.2 (ROW)
unnamed: D65.2 (A), MX60.2 (ROW)
unnamed: D66.2 (A), MX65.2 (ROW)
unnamed: D67.2 (A), MX69.2 (ROW)
unnamed: D68.2 (A), MX72.2 (ROW)
unnamed: D70.5 (CO), D71.2 (CI)
unnamed: D70.6 (DO), D71.1 (DI)
unnamed: D71.5 (CO), D72.2 (CI)
unnamed: D71.6 (DO), D72.1 (DI)
unnamed: D72.5 (CO), D73.2 (CI)
unnamed: D72.6 (DO), D73.1 (DI)
unnamed: D73.5 (CO), D74.2 (CI)
unnamed: D73.6 (DO), D74.1 (DI)
unnamed: D74.5 (CO), D75.2 (CI)
unnamed: D74.6 (DO), D75.1 (DI)
unnamed: D75.5 (CO), D76.2 (CI)
unnamed: D75.6 (DO), D76.1 (DI)
unnamed: D76.5 (CO), D77.2 (CI)
unnamed: D76.6 (DO), D77.1 (DI)
unnamed: D77.5 (CO), D78.2 (CI)
unnamed: D77.6 (DO), D78.1 (DI)
unnamed: D78.5 (CO), D79.2 (CI)
unnamed: D78.6 (DO), D79.1 (DI)
unnamed: D79.5 (CO), D80.2 (CI)
unnamed: D79.6 (DO), D80.1 (DI)
unnamed: D80.5 (CO), D81.2 (CI)
unnamed: D80.6 (DO), D81.1 (DI)
unnamed: D81.5 (CO), D82.2 (CI)
unnamed: D81.6 (DO), D82.1 (DI)
unnamed: D82.5 (CO), D83.2 (CI)
unnamed: D82.6 (DO), D83.1 (DI)
unnamed: D83.5 (CO), D84.2 (CI)
unnamed: D83.6 (DO), D84.1 (DI)
unnamed: Q1.1 (B), R1.1
unnamed: Q1.3 (C), R2.2
unnamed: R7.2, U1.44 (ISET)
unnamed: D70.2 (CI), U2.50 (PA1)
unnamed: D70.1 (DI), U2.51 (PA0)
SCLK: J1.8, J3.3, MX64.1 (COL), U2.11 (PB1)

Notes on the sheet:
Populate R6 only if classic A500 power LED is not connected
Populate either D1 or D69
TODO: - shorten by 1mm on the right side of the PCB (DONE) - Pull-Down for DRVLED (1k) (DONE) - Pull-Up for IN_LED3, IN_LED4 (10k) (DONE) - Pull-Up for SCL,SDA (DONE) - R7: 3.9k Resistor for LED driver (was: 3.3k) (DONE) - Turn Diodes around (DONE) - Bax Logo :-) (done) - Spacebar retention update 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
R10 disables D2 (classic CAPS Led)
R11 enables Digital RGB LEDs (D70-D84)

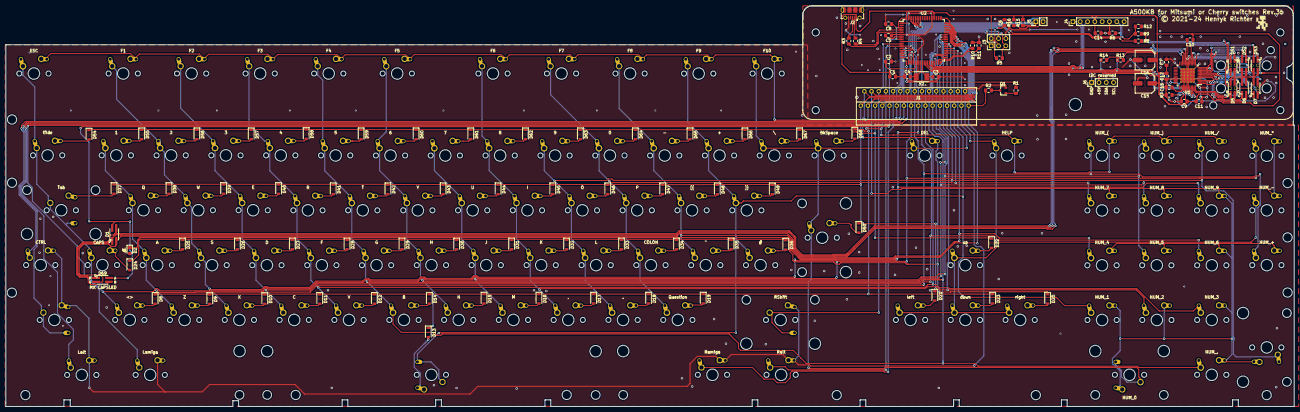
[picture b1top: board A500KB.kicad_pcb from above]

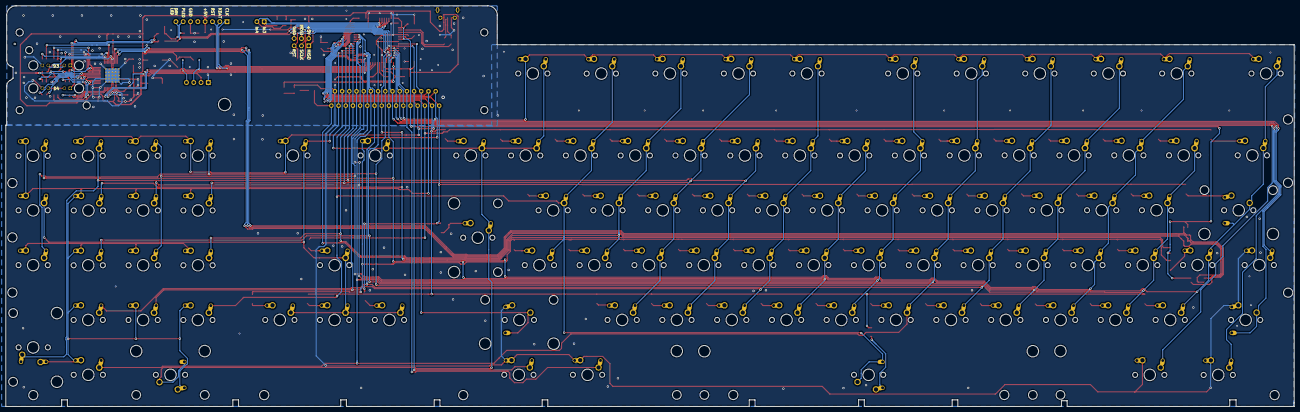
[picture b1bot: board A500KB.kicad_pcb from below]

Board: 2 copper layers, 447.8 x 139.2 mm, 230 parts (2 on the bottom side), 139 nets.

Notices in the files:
PCB/A500KB.kicad_pcb:
© 2021-24 Henryk Richter
